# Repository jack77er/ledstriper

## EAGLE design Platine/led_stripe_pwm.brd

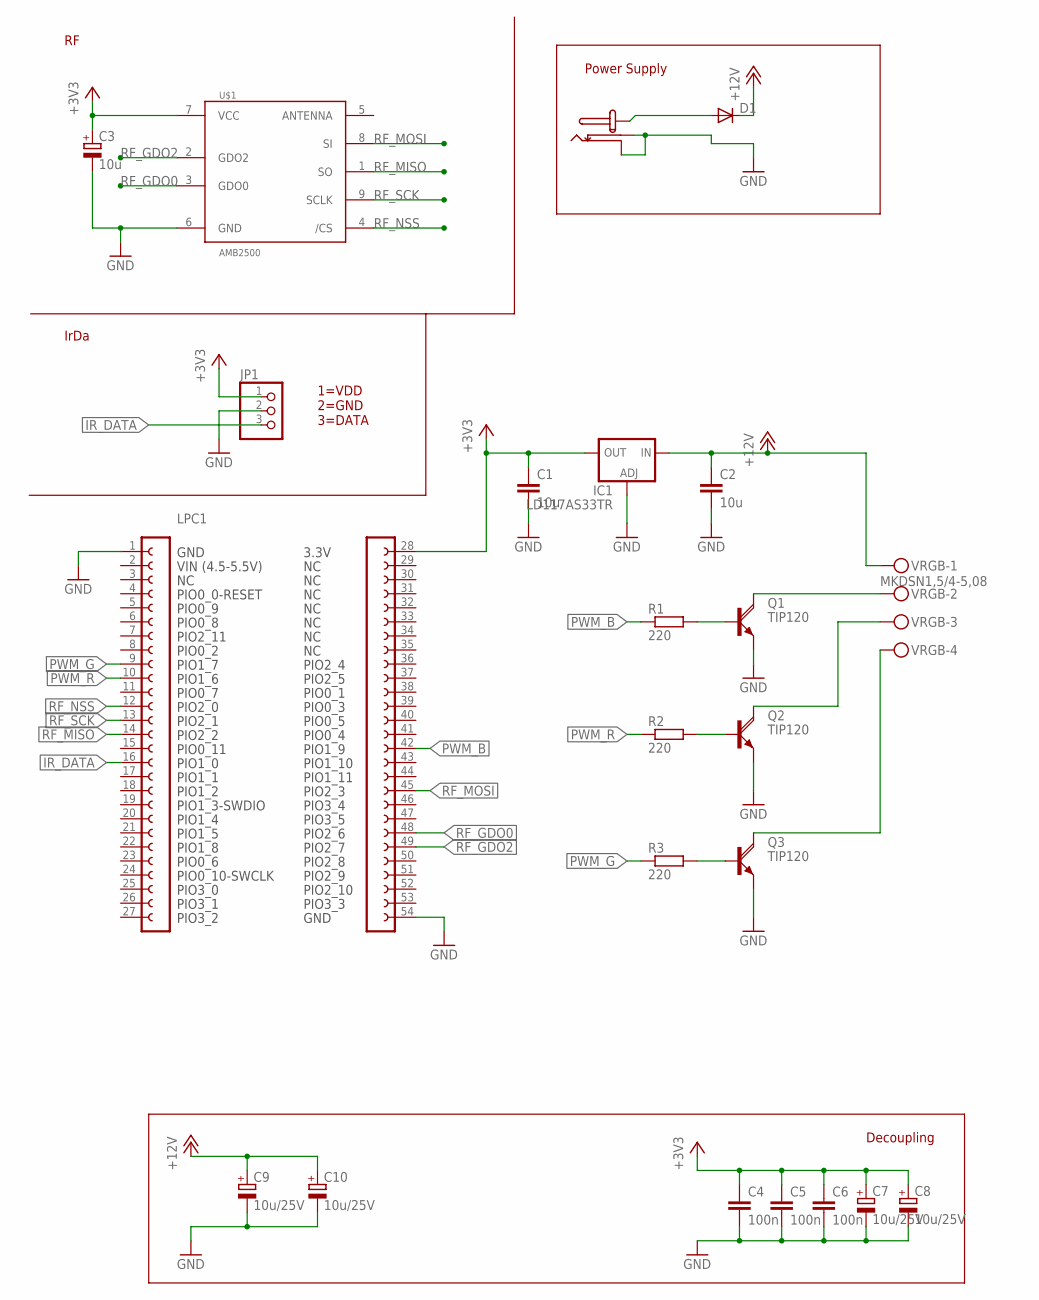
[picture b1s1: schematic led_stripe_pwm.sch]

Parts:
C1, C2: 10u; C0805K
C3: 10u; A/3216-18W
C4, C5, C6: 100n; C0805
C7, C8, C9, C10: 10u/25V; PANASONIC_B
D1: DIODE-DO201-15; DO201-15
IC1: LD117AS33TR; SOT223
JP1: PINHD-1X3; 1X03
LPC1: LPCXPRESSO_LPC1114
Q1, Q2, Q3: TIP120; TO220AH
R1, R2, R3: 220; R0805
U$1: AMB2500; AMB8400
U$2: DC_JACK; DC_JACK_21
VRGB: MKDSN1,5/4-5,08

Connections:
+3V3: C1.1, C3.+, C4.1, C5.1, C6.1, C7.+, C8.+, IC1.4 (OUT), JP1.1, LPC1.28, U$1.7 (VCC)
+12V: C2.1, C9.+, C10.+, D1.C, IC1.3 (IN), VRGB.1
GND: C1.2, C2.2, C3.-, C4.2, C5.2, C6.2, C7.-, C8.-, C9.-, C10.-, IC1.1 (ADJ), JP1.2, LPC1.1, LPC1.54, Q1.E, Q2.E, Q3.E, U$1.6 (GND), U$2.P$2, U$2.P$3
IR_DATA: JP1.3, LPC1.16
unnamed: Q1.B, R1.2
unnamed: Q2.B, R2.2
unnamed: Q3.B, R3.2
unnamed: Q2.C, VRGB.3
unnamed: Q1.C, VRGB.2
unnamed: Q3.C, VRGB.4
unnamed: D1.A, U$2.P$1
PWM_B: LPC1.42, R1.1
PWM_G: LPC1.9, R3.1
PWM_R: LPC1.10, R2.1
RF_GDO0: LPC1.48, U$1.3 (GDO0)
RF_GDO2: LPC1.49, U$1.2 (GDO2)
RF_MISO: LPC1.14, U$1.1 (SO)
RF_MOSI: LPC1.45, U$1.8 (SI)
RF_NSS: LPC1.12, U$1.4 (/CS)
RF_SCK: LPC1.13, U$1.9 (SCLK)

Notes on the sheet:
1=VDD 2=GND 3=DATA
IrDa
Power Supply
Decoupling

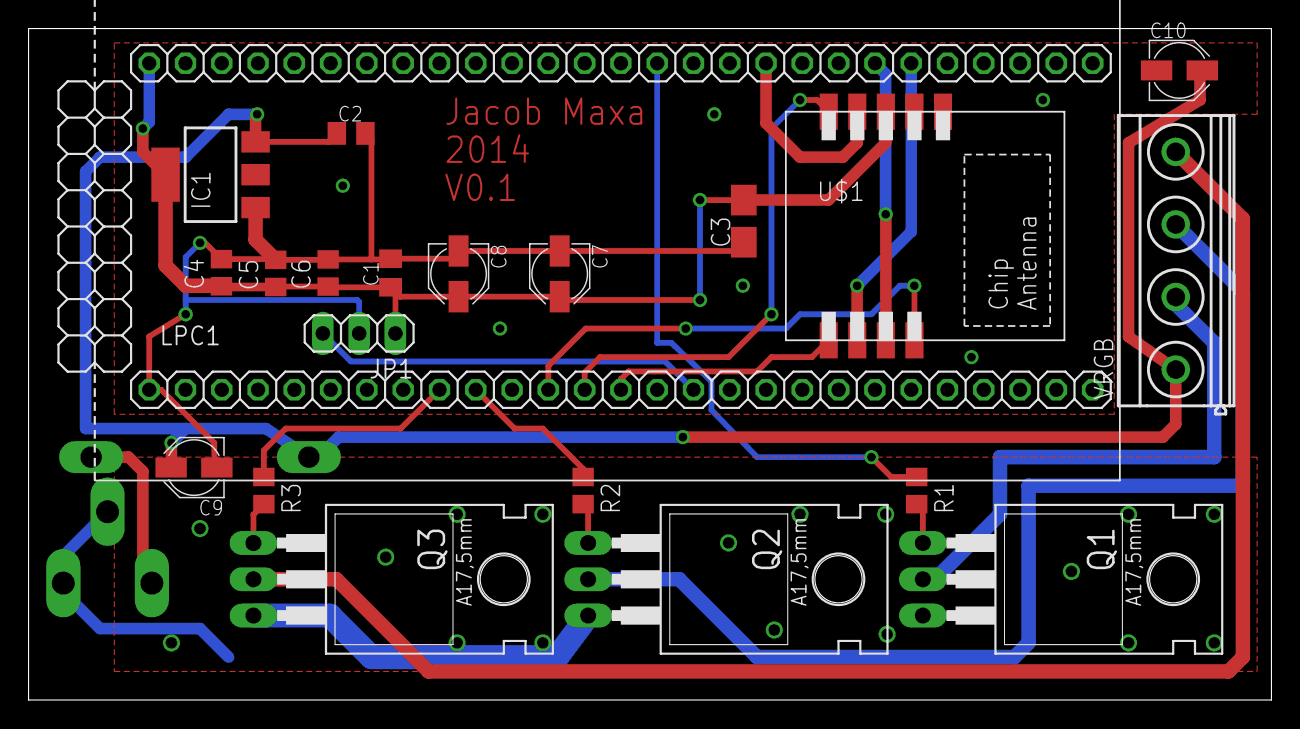
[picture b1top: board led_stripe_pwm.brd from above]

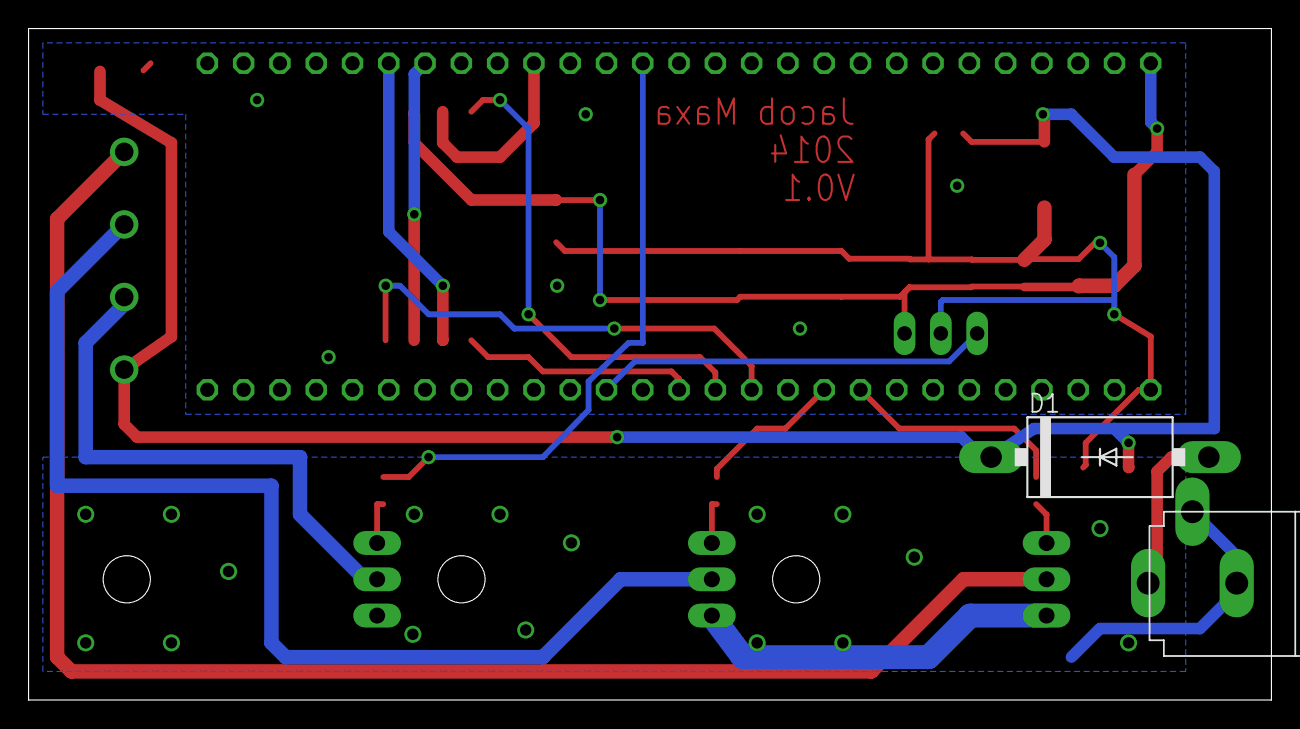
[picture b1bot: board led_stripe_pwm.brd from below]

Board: 2 copper layers, 87.0 x 47.0 mm, 23 parts (2 on the bottom side), 20 nets.
